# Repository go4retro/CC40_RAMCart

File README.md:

## Introduction

Join the growing ranks of Texas Instruments Compact Computer 40 owners who now have increased access to RAM storage on their machine. This CC-40 RAM cartridge replicates the functionality of the original 32kB RAM cartridge option and also expands it 4, 8 or 16 times to  128KB, 256KB, or 512KB.  Easy access DIP switches on the rear of the unit allow one to select which 32kB bank is in use, and all banks are preserved with the optional 3V battery.

Discussion around the design can be reviewed on the AtariAge forum [discussion](https://atariage.com/forums/topic/255728-the-compact-computer-40-cc40/). 

### Main features

- Mimics original PCB location and size
- 4, 8, or 16X capacity
- Easy access to change accessed bank

### Technical Features

- Low power SRAM IC sips battery power when off
- Optional use of P25.2 and P25.3 signals on cartridge port to select RAM bank

## Purchase

This PCB can be purchased in the [RETRO Innovations Online Store](http://store.go4retro.com/ti-compact-computer-40-prototype-boards/).

## License

Copyright (C) 2018  RETRO Innovations

These files are free designs; you can redistribute them and/or modify
them under the terms of the Creative Commons Attribution-ShareAlike 
4.0 International License.

You should have received a copy of the license along with this
work. If not, see <http://creativecommons.org/licenses/by-sa/4.0/>.

These files are distributed in the hope that they will be useful,
but WITHOUT ANY WARRANTY; without even the implied warranty of
MERCHANTABILITY or FITNESS FOR A PARTICULAR PURPOSE.  See the
license for more details.

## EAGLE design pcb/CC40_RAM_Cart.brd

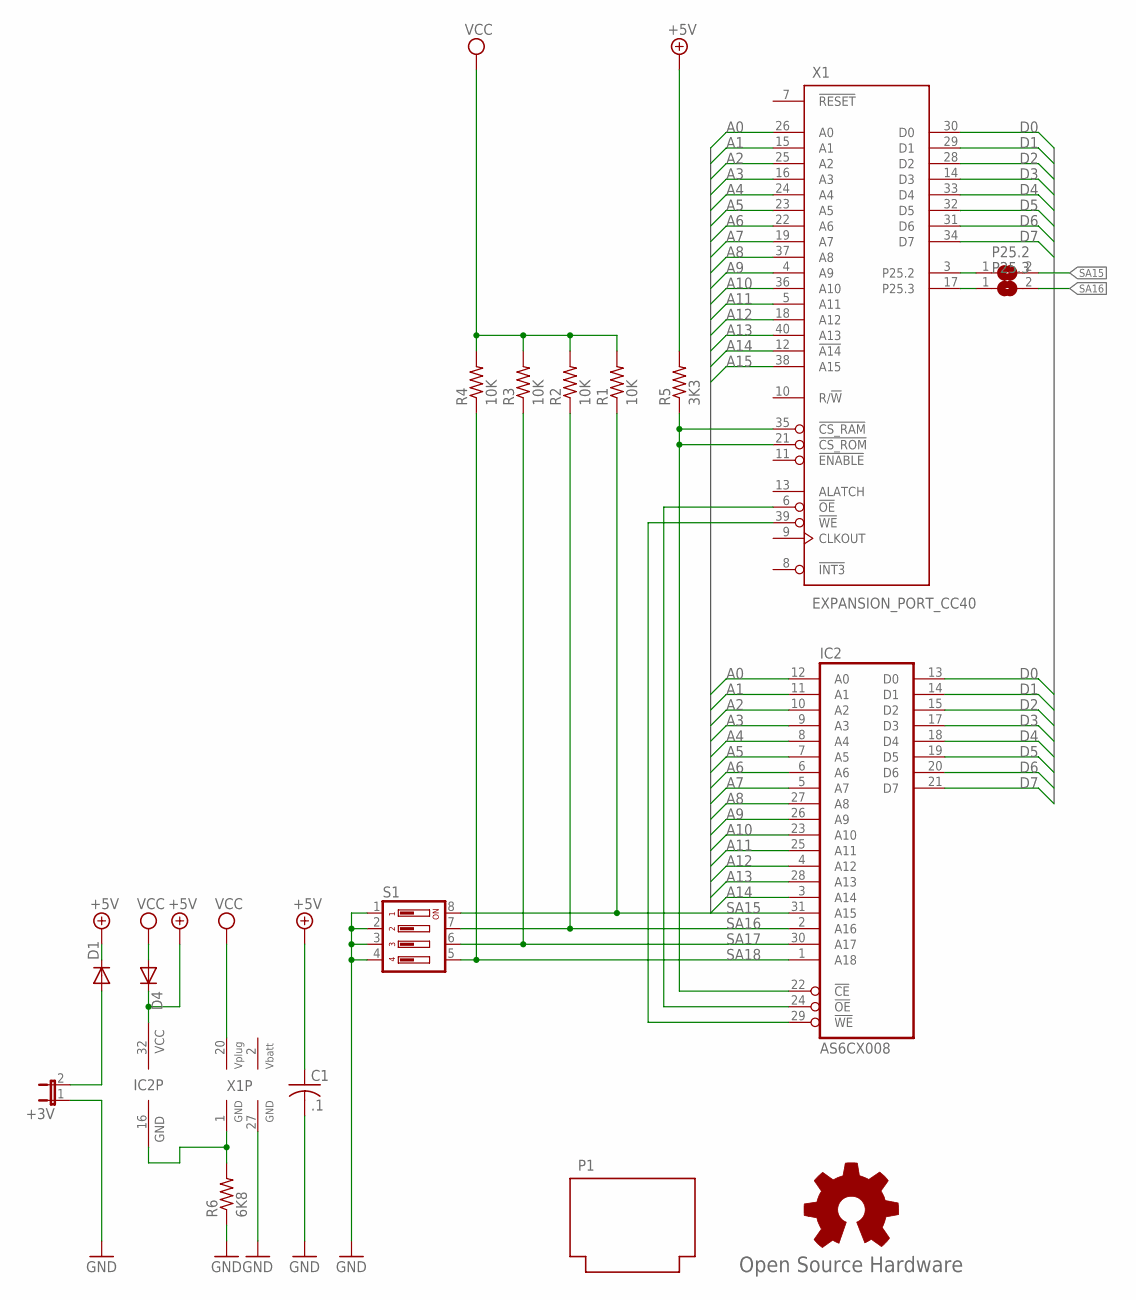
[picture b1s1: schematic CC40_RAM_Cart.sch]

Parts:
+3V: JP1E; JP1
C1: .1; C025-025X050
D1, D4: DIODE-D-5; D-5
GOLD_ORB_SM1: Open Source Hardware; OSHW_8MM
IC2: AS6CX008; DIL32-RP
P1: CC40_CARTN; CC40_CART_NOHOLE
P25.2, P25.3: SJ
R1, R2, R3, R4: 10K; 0204/7
R5: 3K3; 0204/7
R6: 6K8; 0204/7
S1: DP04; DP-04
X1: EXPANSION_PORT_CC40; MA20-2(.050)

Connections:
!OE: IC2.24 (!OE), X1.6 (!OE)
!WE: IC2.29 (!WE), X1.39 (!WE)
+5V: C1.1, D1.C, D4.C, IC2.32 (VCC), R5.2
A0: IC2.12 (A0), X1.26 (A0)
A1: IC2.11 (A1), X1.15 (A1)
A2: IC2.10 (A2), X1.25 (A2)
A3: IC2.9 (A3), X1.16 (A3)
A4: IC2.8 (A4), X1.24 (A4)
A5: IC2.7 (A5), X1.23 (A5)
A6: IC2.6 (A6), X1.22 (A6)
A7: IC2.5 (A7), X1.19 (A7)
A8: IC2.27 (A8), X1.37 (A8)
A9: IC2.26 (A9), X1.4 (A9)
A10: IC2.23 (A10), X1.36 (A10)
A11: IC2.25 (A11), X1.5 (A11)
A12: IC2.4 (A12), X1.18 (A12)
A13: IC2.28 (A13), X1.40 (A13)
A14: IC2.3 (A14), X1.12 (!A14)
A15: X1.38 (A15)
D0: IC2.13 (D0), X1.30 (D0)
D1: IC2.14 (D1), X1.29 (D1)
D2: IC2.15 (D2), X1.28 (D2)
D3: IC2.17 (D3), X1.14 (D3)
D4: IC2.18 (D4), X1.33 (D4)
D5: IC2.19 (D5), X1.32 (D5)
D6: IC2.20 (D6), X1.31 (D6)
D7: IC2.21 (D7), X1.34 (D7)
GND: +3V.1, C1.2, R6.1, S1.1, S1.2, S1.3, S1.4, X1.27 (GND)
unnamed: IC2.22 (!CE), R5.1, X1.21 (!CS_ROM), X1.35 (!CS_RAM)
unnamed: +3V.2, D1.A
unnamed: IC2.16 (GND), R6.2, X1.1 (GND)
P25.2: P25.2.1, X1.3 (P25.2)
P25.3: P25.3.1, X1.17 (P25.3)
SA15: IC2.31 (A15), P25.2.2, R1.1, S1.8
SA16: IC2.2 (A16), P25.3.2, R2.1, S1.7
SA17: IC2.30 (A17), R3.1, S1.6
SA18: IC2.1 (A18), R4.1, S1.5
VBATT: X1.2 (VBATT)
VCC: D4.A, R1.2, R2.2, R3.2, R4.2, X1.20 (VPLUG)

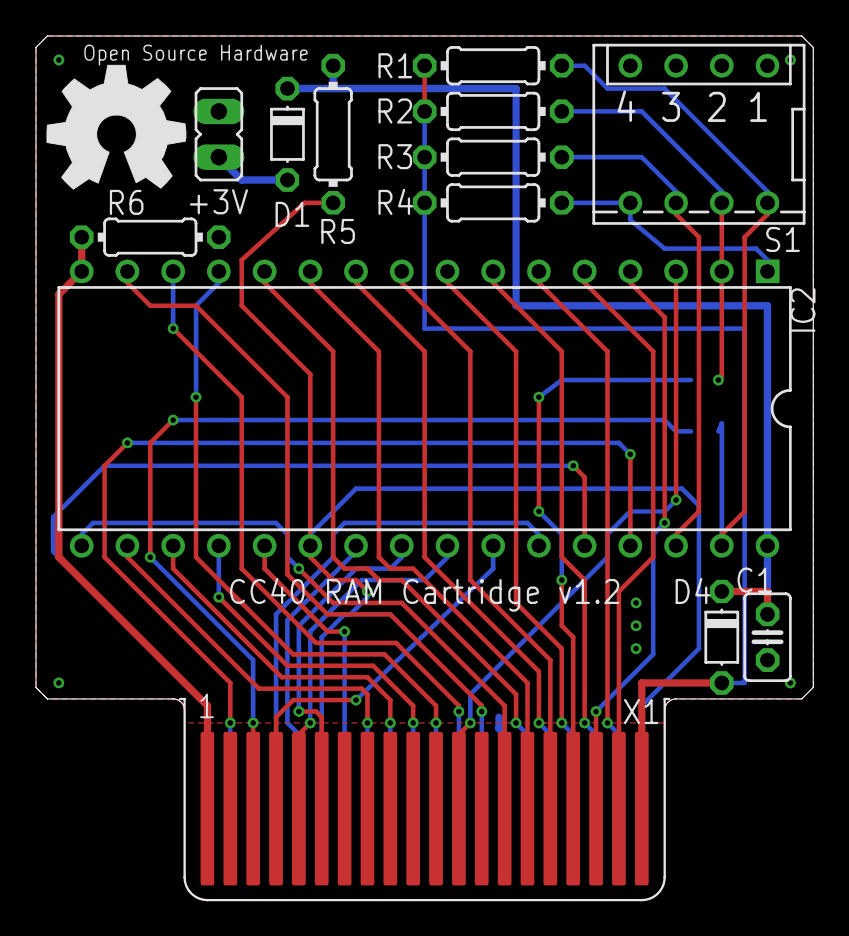
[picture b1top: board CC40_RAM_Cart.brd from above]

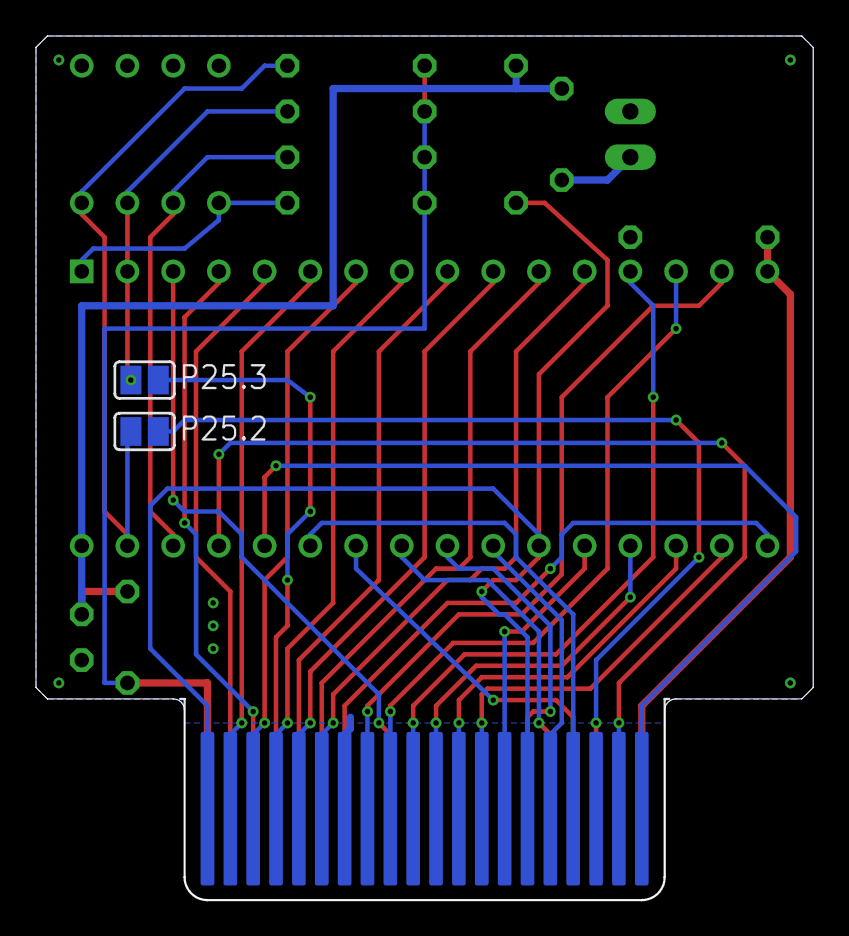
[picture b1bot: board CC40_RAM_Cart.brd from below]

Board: 2 copper layers, 43.2 x 48.0 mm, 17 parts (2 on the bottom side), 37 nets.

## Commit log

2024-07-14 Updated layouts and measurements

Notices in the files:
pcb/CC40_RAM_Cart.brd:
(c) 2017 RETRO Innovations
